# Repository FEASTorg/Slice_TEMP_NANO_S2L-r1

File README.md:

# Slice Template

Template for creating BREAD slices. Features Arduino Nano, small dimensions (70x100mm), 2 layers, and this is the first revision (TEMP_NANO_S2L-r1).

## Introduction

[Short introduction on the project.]

## Usage

[Explain how to use the project. Include examples and screenshots if applicable.]

## Documentation

Please refer to the [docs](/docs) for more info.

---

<div align="center">
  
</div>

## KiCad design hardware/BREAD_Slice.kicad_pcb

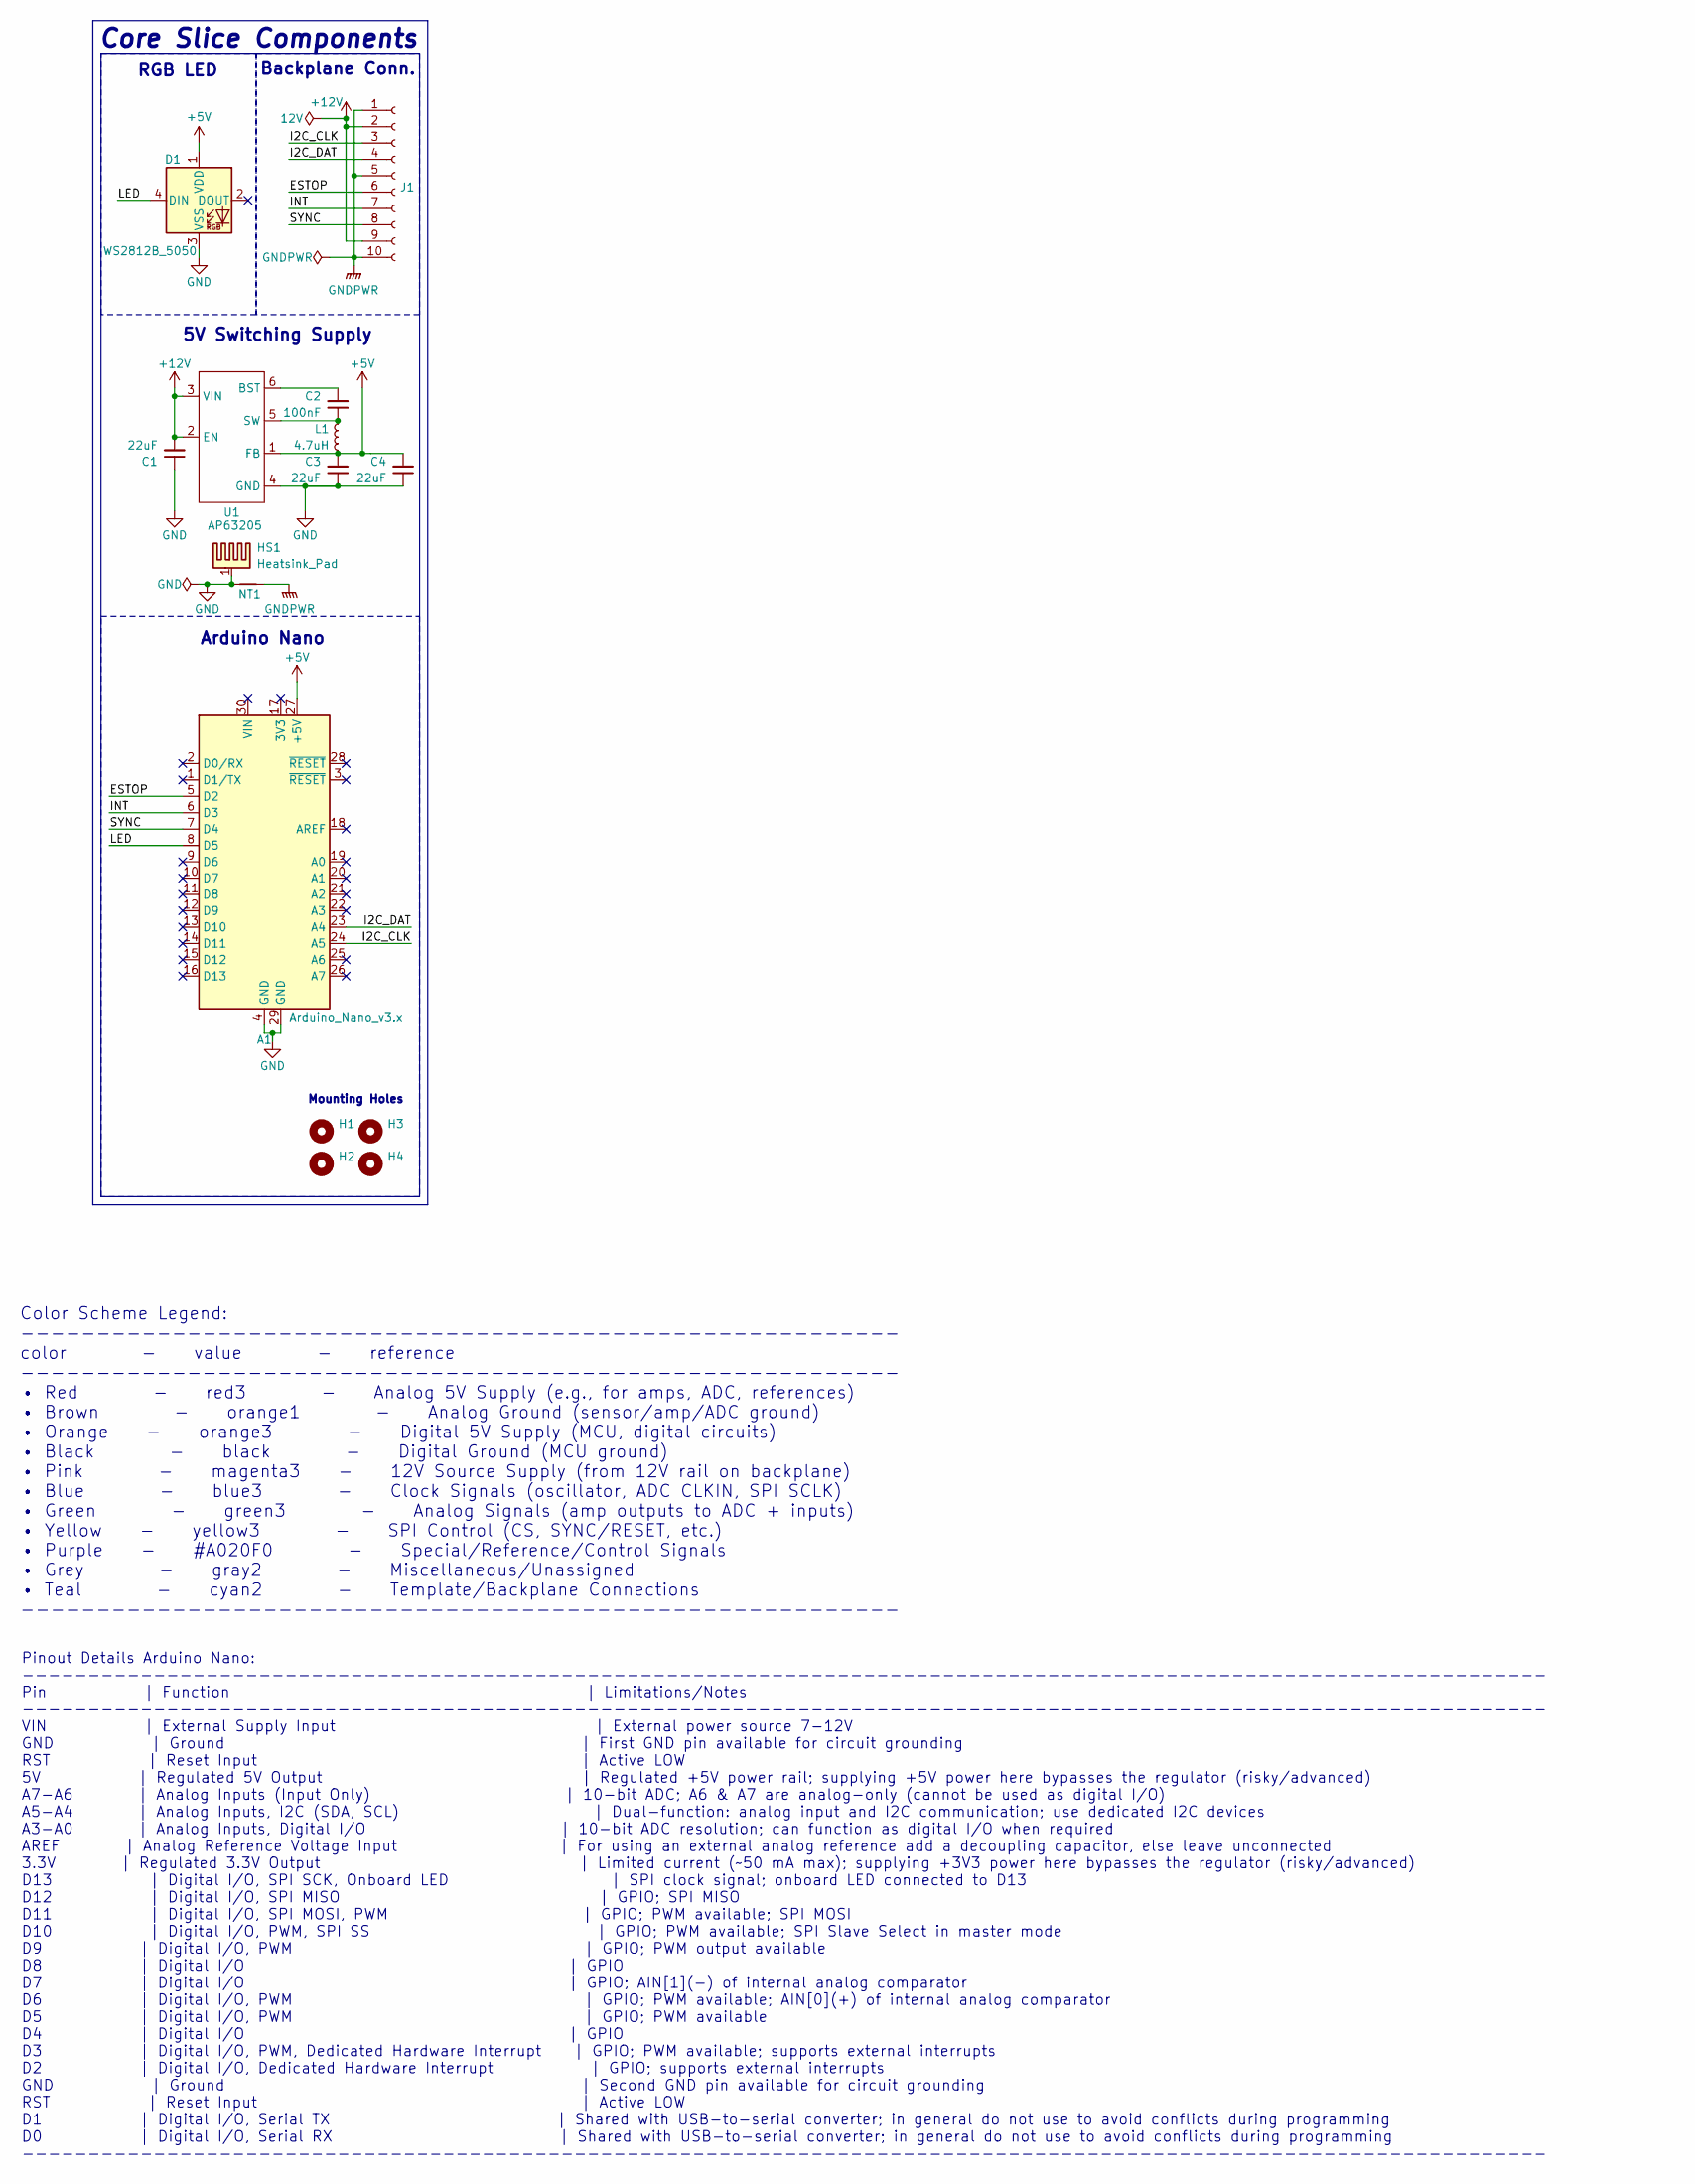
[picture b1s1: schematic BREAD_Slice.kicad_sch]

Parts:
A1: Arduino_Nano_v3.x; Arduino_Nano
C1, C3, C4: 22uF; C_1206_3216Metric
C2: 100nF; C_1206_3216Metric
D1: WS2812B_5050; WS2812-5050-4PIN
H1, H2, H3, H4: MountingHole; MountingHole_5mm
HS1: Heatsink_Pad; Thermal_Pad
J1: Conn_01x10_Female; PinSocket_1x10_P2.54mm_Horizontal
L1: 4.7uH; L_1210_3225Metric
NT1: NetTie_2; NetTie-2_SMD_Pad2.0mm
U1: AP63205; TSOT-23-6

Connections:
+5V: A1.27 (+5V), C3.2, C4.2, D1.1 (VDD), L1.2, U1.1 (FB)
+12V: C1.2, J1.2, J1.9, U1.2 (EN), U1.3 (VIN)
/ESTOP: A1.5 (D2), J1.6
/I2C_CLK: A1.24 (A5), J1.3
/I2C_DAT: A1.23 (A4), J1.4
/INT: A1.6 (D3), J1.7
/LED: A1.8 (D5), D1.4 (DIN)
/SYNC: A1.7 (D4), J1.8
GND: A1.4 (GND), A1.29 (GND), C1.1, C3.1, C4.1, D1.3 (VSS), HS1.1, NT1.1, U1.4 (GND)
GNDPWR: J1.1, J1.5, J1.10, NT1.2
unnamed: C2.2, U1.6 (BST)
unnamed: C2.1, L1.1, U1.5 (SW)

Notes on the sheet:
5V Switching Supply
Pinout Details Arduino Nano: -------------------------------------------------------------------------------------------------------------------- Pin | Function | Limitations/Notes -------------------------------------------------------------------------------------------------------------------- V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
RGB LED
Color Scheme Legend: ---------------------------------------------------------- color - value - reference ---------------------------------------------------------- • Red - red3 - Analog 5V Supply (e.g., for amps, ADC, references) • Brown - orange1 - Analog Ground (sensor/amp/ADC ground) • Orange -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
Core Slice Components
Arduino Nano
Mounting Holes
Backplane Conn.

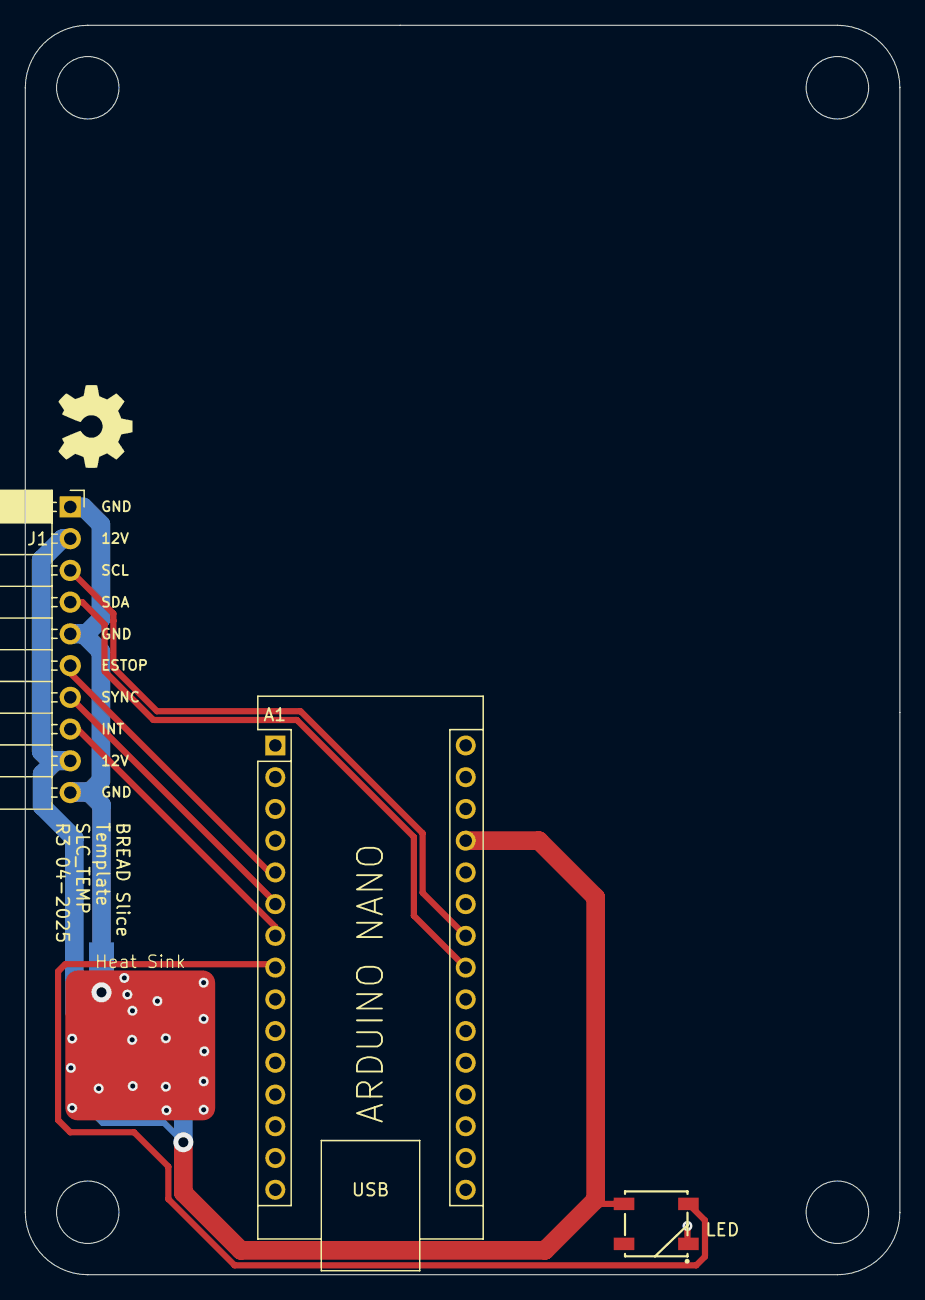
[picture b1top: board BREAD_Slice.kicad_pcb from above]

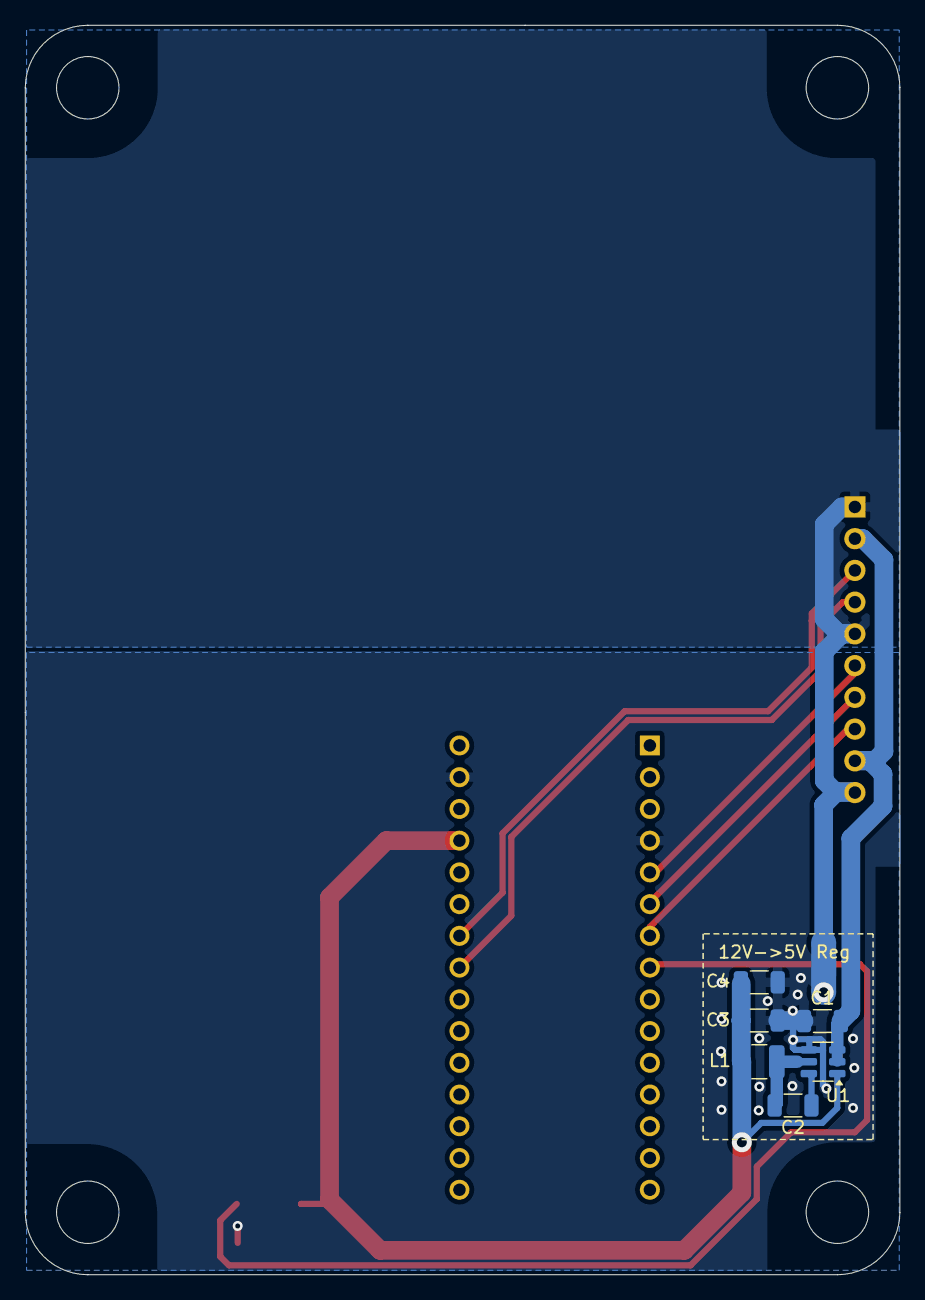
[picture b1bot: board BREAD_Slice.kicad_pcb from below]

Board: 2 copper layers, 70.0 x 100.0 mm, 16 parts (7 on the bottom side), 12 nets.

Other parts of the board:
Logo1: Logo_Open_Hardware_Small; OSHW-Symbol_6.7x6mm_SilkScreen

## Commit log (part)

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2025-09-24 remove old ones
2025-09-24 📄 KiBot index + board renders (auto)
2025-09-24 remove nucleo assets
2026-01-26 update gitignore
2026-01-26 review and revise board and update footprints
2026-04-20 refactor: org casing rename from 'FEASTorg' to 'feastorg'
2026-05-20 Add slice.yaml manifest (schema v1.0)
2026-05-24 Add standardized TODO.md with Pass 1/Pass 2 structure
